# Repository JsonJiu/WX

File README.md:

# 云达诺项目 - V1.0.1

本仓库包含云达诺FM33LG0XX测试系统的代码。

## 目录结构

- **云达诺/** - 主项目代码目录
  - `Drivers/` - 驱动程序
  - `Inc/` - 头文件
  - `Src/` - 源代码文件
  - `MDK-ARM/` - Keil MDK工程文件
  - `MF-config/` - 配置文件
  - `README.md` - 项目说明
  - `README_V1.0.1.md` - V1.0.1版本更新说明

## 版本说明

当前版本：**V1.0.1**

查看详细更新内容：[云达诺/README_V1.0.1.md](./云达诺/README_V1.0.1.md)

## V1.0.1 主要更新

- ✅ 工位检测扩展至10个工位
- ✅ 新增独立阀门测试流程
- ✅ 优化阀门开关检测逻辑
- ✅ 压力检测功能更新
- ✅ 测试流程优化

## 快速开始

1. 克隆仓库
2. 使用Keil MDK打开 `云达诺/MDK-ARM/FM33LG0XX_Tester.uvprojx`
3. 编译并下载到目标设备

## 分支说明

- `main` - 主分支
- `v1.0.1` - V1.0.1版本分支

---

开发团队：云达诺开发组

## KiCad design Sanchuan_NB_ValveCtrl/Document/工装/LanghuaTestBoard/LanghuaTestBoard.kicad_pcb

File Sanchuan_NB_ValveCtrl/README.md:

# Sanchuan_NB_ValveCtrl

三川 NB-IoT 阀控水表测试工装程序

## 版本信息

- **当前版本**: 1.0.0
- **发布日期**: 2024-12-01
- **硬件平台**: FM33LG04x (Cortex-M0+)

## 项目说明

本项目为三川 NB-IoT 阀控水表的测试工装程序，用于生产线水表测试。

### 主要功能

- 水表通信协议测试
- 阀门控制测试
- 电流检测
- LED 状态指示
- 透传模式支持

## 编译环境

- **编译器**: ARM GCC 10 2021.10
- **构建系统**: CMake + Ninja
- **烧录工具**: PyOCD

## 快速开始

### Windows 编译

```bash
# 配置 (首次)
cmake.exe -S . -B build_fast -DCMAKE_BUILD_TYPE=Release -G Ninja

# 编译
cmake.exe --build build_fast --parallel

# 烧录
pyocd flash build_fast/Sanchuan_NB_ValveCtrl.elf --target fm33lg04x
```

### Linux 编译

```bash
# 配置 (首次)
cmake -S . -B build_fast -DCMAKE_BUILD_TYPE=Release -G Ninja

# 编译
cmake --build build_fast --parallel
```

## 目录结构

```
├── CMakeLists.txt      # CMake 构建配置
├── Src/                # 应用源代码
├── Inc/                # 应用头文件
├── Drivers/            # FM33LG0xx 驱动库
├── MF-config/          # 外设配置
├── VscodeGcc/          # VSCode + GCC 配置
├── MDK-ARM/            # Keil MDK 工程 (可选)
└── Document/           # 相关文档
```

## 版本历史

### v1.0.0 (2024-12-01)
- 初始版本
- 从浪花项目移植
- 重命名为 Sanchuan_NB_ValveCtrl

## 作者

Aspiring-Freeman

## 许可证

本项目基于 Mulan PSL v2 许可证开源。

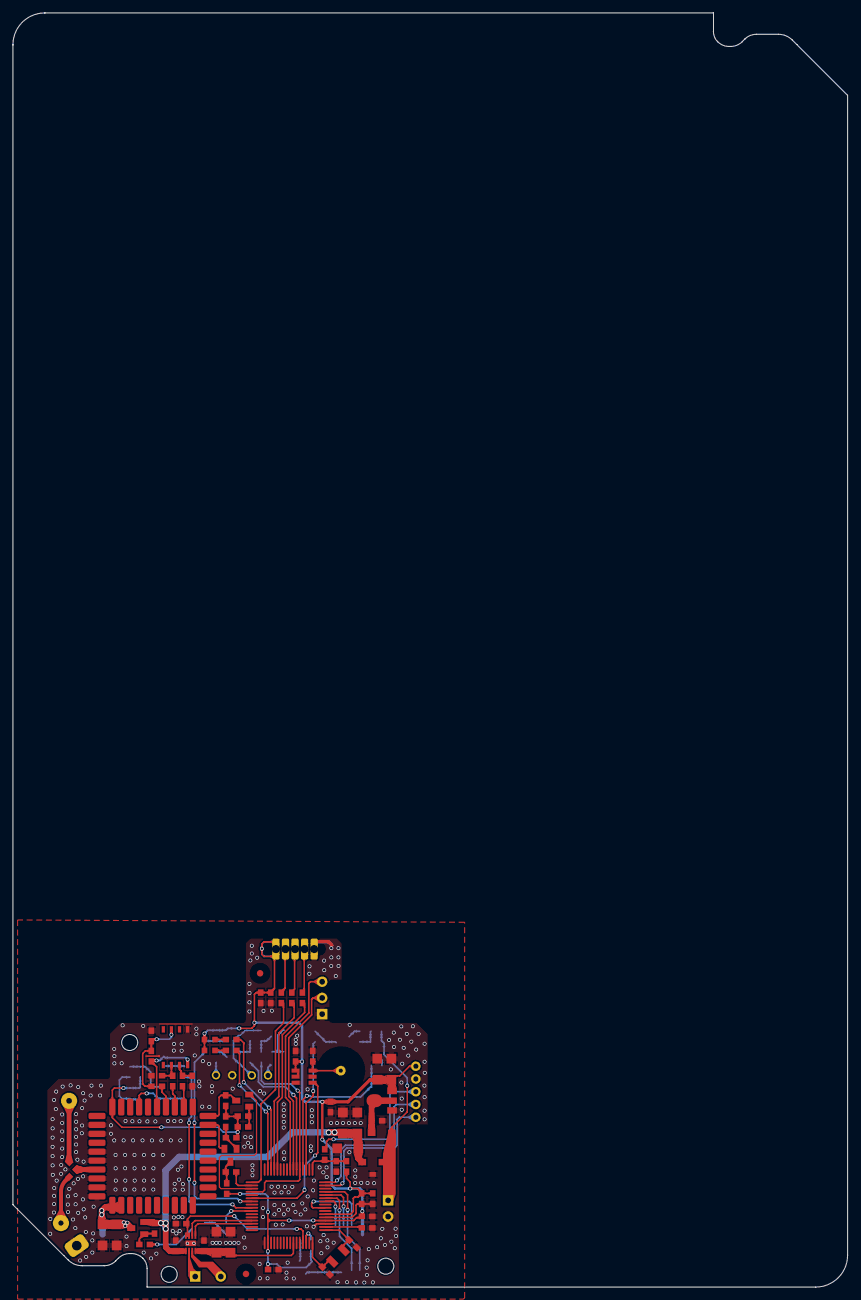
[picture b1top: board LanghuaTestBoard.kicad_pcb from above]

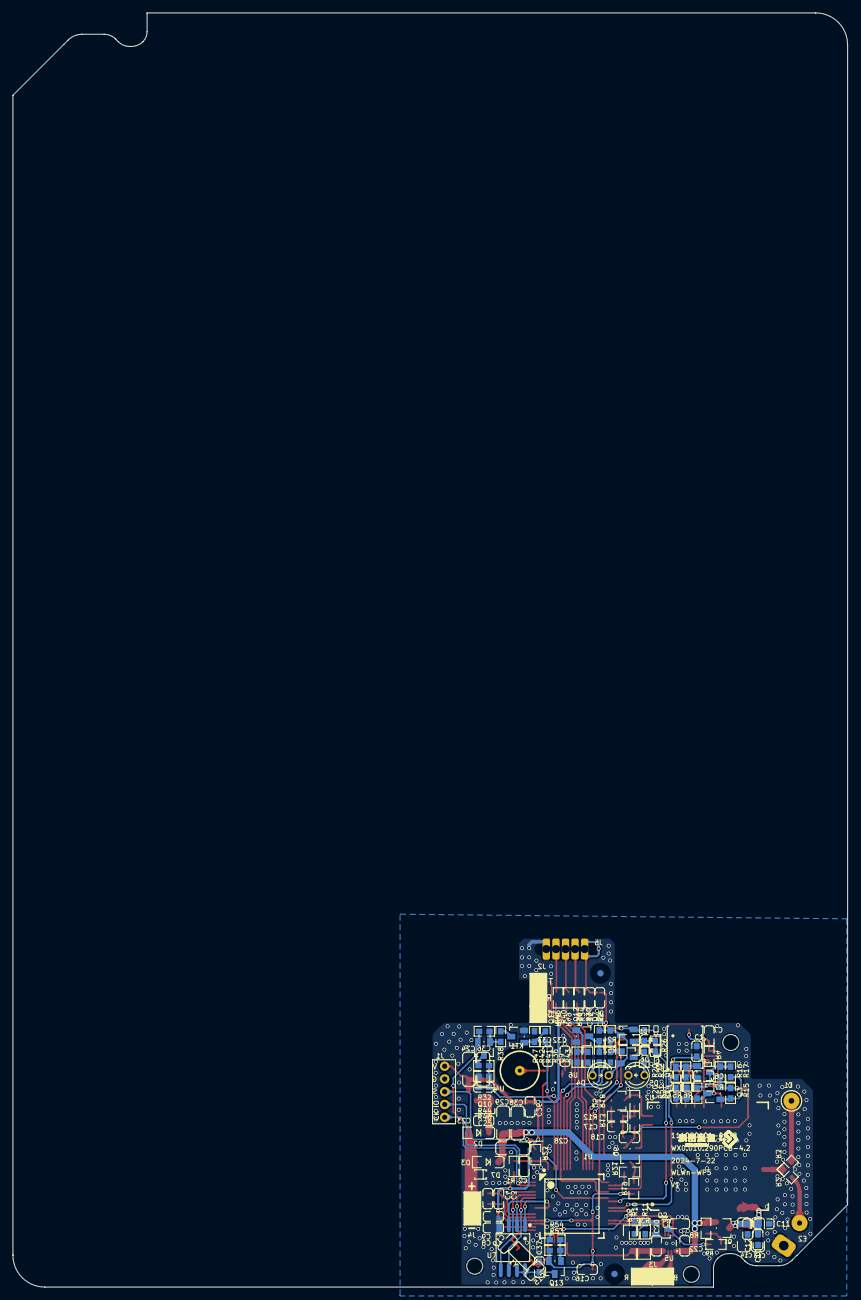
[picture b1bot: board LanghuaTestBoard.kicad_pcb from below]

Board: 2 copper layers, 130.8 x 199.7 mm, 126 parts (45 on the bottom side), 85 nets.

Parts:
C1, C2, C3, C8, C9, C12, C16, C21, C22, C26, C32, C34, C37: 100nF; C0603
C4: 10μF/10V; C0603
C5, C6, C7, C20: 33pF; C0603
C10, C15, C19: 22pF; C0603
C11, C23: 100pF; C0603
C13, C14, C24, C28, C29, C36, C38: 100uF; C1206
C17, C18: 1nF; C0603
C25: 12pF; C0603
C30: 10nF; C0603
C33: 4.7pF; C0603
C35: 1uF; C0603
D1, D6: Red; LED-0603
D2, D3: DSK14; SOD-123
D4: AT403; LED-3
D5: AT203-立; LED-3
D7: XE3D5VB; SOD-323_L1.8-W1.3-LS2.5-RD
E1: ANT-1
E2: ANTENNA_3; ANT-3
H1, H2, H4: HOLE-2.5
J1: CON5-2.0; J_DIP_2.0_1*05_H
J2: CON3; SIP-3
J3: CON2; SIP-2-4mm
J4: CON2; SIP-2
J5: BCON-B5
KT1: Touch; TOUCH-1
LABEL1, LABEL2, LABEL3, LABEL4: MARK
Q1, Q7, Q9, Q10: CJ2301; SOT-23
Q2, Q4, Q5, Q6, Q11, Q12: S8050; SOT-23
Q3, Q13: S8550; SOT-23
R1, R4, R9, R16, R18, R19, R38, R51, R54: 10kΩ±5%; R0603
R2, R3, R14, R21, R23, R41: 0Ω±5%; R0603
R5, R6, R7: 22Ω±5%; R0603
R8, R53: 200KΩ±5%; R0603
R10, R12, R13, R17, R20, R40: 4.7kΩ±5%; R0603
R11, R15, R22, R45, R47: 47K±5%; R0603
R24, R26, R36, R52: 1kΩ±5%; R0603
R25, R30, R32: 1MΩ±5%; R0603
R34: 100kΩ±5%; R0603
R35, R37: 1Ω±1%; R1206
R42: 20kΩ±5%; R0603
R43, R48, R49, R50: 100Ω±5%; R0603
R44: 20K±1%; R0603
R46: 10kΩ±1%; R0603
U1: FM33LE026; LQFP-64_L10.0-W10.0-P0.50-LS12.0-BL
U2: UMN601-M1; MB26-Y0B
U3: ESIM; MFF2
U4: CE6232A33P; SOT89
U5: DRV8837; WSON-8
U6: TTP233H; SOT-23-6
U7: P25Q32H-SUH-IR; SOIC-8
Y1: 32.768K; Y3215

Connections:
AIN8: C30.2, R35.2, R37.2, U1.42, U5.4
ANT: R2.1, R3.2, U2.27
CTR_F_VCC: R54.1, U1.46
DB_RXD: J2.2, U1.7
DB_TXD: J2.3, U1.8
DRV+: J3.1, U5.2
DRV-: J3.2, U5.3
EXTI1: R48.1, U1.12
EXTI2: R49.1, U1.13
EXTI3: R50.1, U1.17
EXTI4: R41.2, U1.5, U1.20
FLASH_CLK: U1.59, U7.6
FLASH_CS: U1.58, U7.1
FLASH_MISO: U1.60, U7.2
FLASH_MOSI: U1.61, U7.5
FLASH_VCC: C37.2, Q13.3, U7.7, U7.8
FLASH_WP: U1.56, U7.3
GND: C1.1, C2.1, C3.1, C4.1, C5.1, C6.1, C7.2, C8.1, C9.1, C10.1, C11.1, C12.1, C13.1, C14.1, C15.1, C16.1, C19.1, C20.1, C21.1, C22.2, C23.1, C24.1, C25.1, C26.1, C28.1, C29.1, C30.1, C32.2, C33.1, C34.1, C35.1, C36.1, C37.1, C38.1, D5.2, D7.1, E2.2, J1.2, J2.1, J4.2, J5.1, Q2.2, Q4.2, Q11.2, Q12.2, R11.1, R22.1, R35.1, R37.1, R45.1, R46.2, R47.1, R51.1, U1.33, U1.51, U1.53, U2.22, U2.23, U2.25, U2.26, U2.28, U2.29, U2.30, U3.1, U4.1, U5.0, U6.2, U6.6, U7.4
IR_EN: R26.1, U1.23
IR_TX: R36.1, U1.6
KEY: U1.22, U6.1
LED0: R24.2, U1.14
LED1: R52.2, U1.15
NB_ON: R10.1, U1.26
NB_RST: C20.2, Q3.3, R14.2, R51.2, U2.17
NB_RST_MCU: R20.2, U1.25
NB_RX: Q5.3, R18.1, U2.10
NB_RX_MCU: R21.2, U1.18
NB_TX: Q6.2, U2.9
NB_TX_MCU: Q5.2, U1.19
NetC5_2: C5.2, R5.1, U3.7
NetC6_2: C6.2, R6.1, U3.6
NetC7_1: C7.1, R4.1, R7.1, U3.3
NetC8_2: C8.2, U1.50
NetC17_1: C17.1, Q5.1, R12.2
NetC18_2: C18.2, Q6.1, R13.1
NetC23_2: C23.2, D2.2, U4.3
NetC33_2: C33.2, KT1.1, U6.3
NetD1_2: D1.2, R24.1
NetD4_1: D4.1, R42.2
NetD4_2: D4.2, Q7.3, Q9.2, R30.2, R34.2
NetD5_1: D5.1, R43.1
NetD6_2: D6.2, R52.1
NetE1_1: E1.1, R3.1
NetE2_1: E2.1, R2.2
NetJ1_3: J1.3, R23.2
NetJ5_2: J5.2, R48.2
NetJ5_3: J5.3, R49.2
NetJ5_4: J5.4, R50.2
NetQ1_1: Q1.1, R8.1, R9.2
NetQ2_1: Q2.1, R10.2, R11.2
NetQ2_3: Q2.3, R9.1
NetQ3_1: Q3.1, R15.1, R17.2
NetQ4_1: Q4.1, R20.1, R22.2
NetQ4_3: Q4.3, R14.1, R16.1, R17.1
NetQ6_3: Q6.3, R19.2, R21.1
NetQ7_1: Q7.1, R25.1, R26.2
NetQ9_1: Q9.1, R30.1, R36.2
NetQ9_3: Q9.3, R43.2
NetQ10_1: Q10.1, R32.1, R38.2
NetQ10_3: Q10.3, R44.1
NetQ11_1: Q11.1, R40.2, R45.2
NetQ11_3: Q11.3, R38.1
NetQ12_1: Q12.1, R42.1, R47.2
NetQ12_3: Q12.3, R34.1, R41.1
NetQ13_1: Q13.1, R53.1, R54.2
NetR5_2: R5.2, U2.12
NetR6_2: R6.2, U2.13
NetR7_2: R7.2, U2.14
OUT_A: U1.29, U5.6
OUT_B: U1.30, U5.5
OUT_EN: C21.2, U1.45, U5.7, U5.8
RESET: C2.2, R1.1, R23.1, U1.1
SVS: C25.2, R44.2, R46.1, U1.4
SVS_EN: R40.1, U1.3
SWCLK: J1.5, U1.63
SWDIO: J1.4, U1.64
USIM_VDD: C1.2, R4.2, U2.15, U3.8
VBAT: D2.1, D3.1, D7.2, J4.1, Q10.2, R32.2
VCC: C3.2, C4.2, C9.2, C16.2, C24.2, C26.2, C32.1, C34.2, C35.2, C36.2, D1.1, D6.1, J1.1, J5.5, Q7.2, Q13.2, R1.2, R19.1, R25.2, R53.2, U1.34, U1.52, U1.54, U4.2, U6.4, U6.5
VCC_M: C22.1, C28.2, C29.2, C38.2, D3.2, Q1.2, R8.2, U5.1
VDD_IO: C17.2, C18.1, Q3.2, R12.1, R13.2, R15.2, R16.2, R18.2, U2.20
VDD_NB: C10.2, C11.2, C12.2, C13.2, C14.2, Q1.3, U2.31, U2.32
XT1: C15.2, U1.48, Y1.2
XT2: C19.2, U1.49, Y1.1

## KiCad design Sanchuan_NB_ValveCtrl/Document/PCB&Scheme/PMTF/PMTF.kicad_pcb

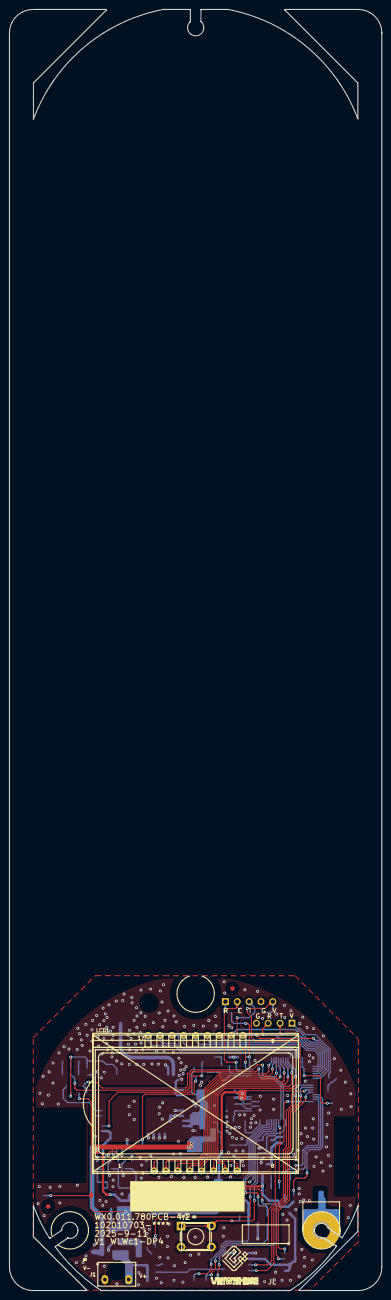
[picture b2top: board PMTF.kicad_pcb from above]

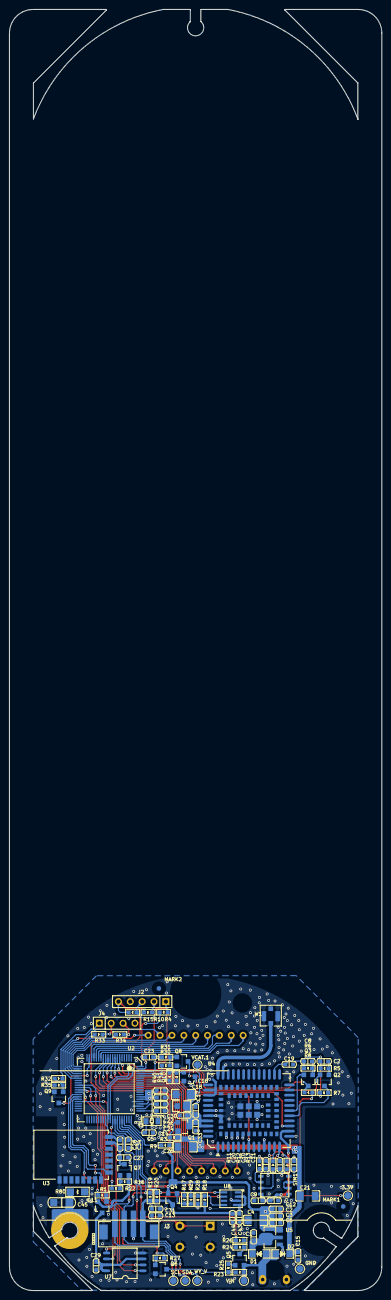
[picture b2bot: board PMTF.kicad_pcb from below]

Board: 2 copper layers, 79.7 x 274.3 mm, 109 parts (106 on the bottom side), 86 nets.

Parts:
3.3V: TEST-PAD
*1: Bar Code1
C1, C2, C9, C13, C15, C22, C24, C25, C29, C30: 100nF/50V; CAP0603
C3, C27, C31, C43: 10uF/10V; CAP0603
C4, C16, C21, C26: 100uF/6.3V; GRM1206
C5, C14: 12pF/50V; CAP0603
C6: 22pF/50V; CAP0603
C7, C8: 1nF/50V; CAP0603
C10, C11, C12, C17, C20, C23, C44: 33pF/50V; CAP0603
C18: 22uF/10V; CAP0805
C19, C28: 1uF/16V; CAP0603
C33, C34: 10pF/50V; CAP0603
C45: 103P/1KV; CAP1206
D1, D2: DS36W; SOD-123FL
GND: TEST-PAD
J1: Header 2; VBAT
J2: Header 5; PIN254_1*5SR
J3: CON4; WX-PH-4AB
J4: XH254_4P; HDR1X4_2.54
LCD1: LCD; JR-H25903AFP
MARK1, MARK2: MARK
Q1, Q4, Q7: UT3401ZG; SOT-23
Q2, Q3, Q6, Q8, Q9, Q10: NPNS-9013; SOT-23
Q5, Q11: PNPS-9012; SOT-23
R1, R30, R32, R40: 3K 5%; RES0603
R3, R16, R17: 2M 5%; RES0603
R4: 100R 5%; RES0603
R5, R6, R7, R8: 4.7K 5%; RES0603
R9, R22, R29: 200K 5%; RES0603
R10, R15, R18, R28: 10K 1%; RES0603
R11, R12, R13: 22R 5%; RES0603
R19, R20, R31, R41: 10K 5%; RES0603
R23: 200k; RES0603
R24: 330K 5%; RES0603
R25, R27: 10k; RES0603
R26: 220K 5%; RES0603
R33, R34, R35: 1K 5%; RES0603
R80: 1M 5%; RES1206
SCL: TEST-PAD
SDA: TEST-PAD
SIM1: SIM IC; SIMIC
SW1: KEY; DIP-6X6X8
U2: FM33LG0x8; LQFP80
U3: DB809
U4: EC801E
U5: CE6232A33P; SOT-89
U7: P25Q80H-SUH-IR; SOP-8L-200MIL
U8: HP303B; LGA_8
VCAT.1: TEST-PAD
VIN: TEST-PAD
W1: 天线; ANT-IPEX_1
WY_V: TEST-PAD
Y1: SF32WK32768D71T005; SMD-3215_2P

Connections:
3.3V: 3.3V.1, C2.1, C3.1, C4.1, C6.1, C22.2, C25.2, J2.5, Q4.2, Q7.2, Q11.2, R8.2, R10.2, R15.1, R16.2, R17.2, U2.64, U2.66, U2.67, U5.3
CAT.1-RESET: Q8.3, U4.15
CAT.1-RXD: Q2.3, R7.1, U4.17
CAT.1-TXD: Q3.2, U4.18
CAT.1_KEY: R40.1, U2.76
CAT.1_PWR: R9.1, U2.57
CAT.1_VCC: C16.1, C17.1, C18.1, C30.2, C33.1, Q1.3, U4.42, U4.43, VCAT.1.1
CAT.1_VIN: C15.1, C21.1, C26.1, D2.2, Q1.2, R3.2
CHEAK_POWER: R27.1, U2.52
COM0: LCD1.1, U2.6
COM1: LCD1.2, U2.7
COM2: LCD1.3, U2.8
COM3: LCD1.4, U2.9
EARTH: C45.1, R80.2
FLASH_CLK: U2.30, U7.6
FLASH_CS: U2.29, U7.1
FLASH_CTL: R1.1, U2.33
FLASH_MISO: U2.31, U7.2
FLASH_MOSI: U2.32, U7.5
GND: C1.2, C2.2, C3.2, C4.2, C5.1, C6.2, C9.2, C10.1, C11.1, C12.2, C13.2, C14.1, C15.2, C16.2, C17.2, C18.2, C19.2, C20.1, C21.2, C22.1, C23.1, C24.2, C25.1, C26.2, C27.2, C28.2, C29.2, C30.1, C31.2, C33.2, C34.1, C43.2, C44.2, C45.2, GND.1, J1.1, J2.4, J3.2, J3.5, J3.6, J4.4, Q6.2, Q8.2, Q9.2, Q10.2, R26.1, R28.2, R31.1, R35.1, R41.2, R80.1, SIM1.1, SW1.2, U2.63, U2.65, U3.1, U3.15, U4.1, U4.10, U4.27, U4.34, U4.36, U4.37, U4.40, U4.41, U4.45, U4.46, U4.47, U4.48, U4.70, U4.71, U4.72, U4.73, U4.88, U4.89, U4.90, U4.91, U4.92, U4.93, U4.94, U4.95, U5.1, U7.4, U8.2, W1.2
GPRS_RST: R30.1, U2.77
LVDIN: C34.2, R24.1, R26.2, U2.53
MCU_RXD2: Q3.3, R8.1, U2.50
MCU_TXD2: Q2.2, U2.51
NetC1_1: C1.1, D1.2, U5.2
NetC7_2: C7.2, Q2.1, R5.2
NetC8_2: C8.2, Q3.1, R6.2
NetC24_1: C24.1, U2.62
NetC27_1: C27.1, C28.1, Q7.3, U3.14
NetC29_1: C29.1, Q11.3, U7.3, U7.7, U7.8
NetJ2_1: J2.1, R4.2
NetJ4_1: J4.1, R32.1
NetJ4_2: J4.2, R33.1
NetJ4_3: J4.3, R34.1
NetQ1_1: Q1.1, R3.1, R9.2
NetQ4_1: Q4.1, R17.1, R29.2
NetQ5_1: Q5.1, R25.2
NetQ5_3: Q5.3, R24.2
NetQ6_1: Q6.1, R27.2
NetQ6_3: Q6.3, R23.1, R25.1
NetQ7_1: Q7.1, R16.1, R22.2
NetQ8_1: Q8.1, R30.2, R31.2
NetQ9_1: Q9.1, R32.2, R35.2
NetQ10_1: Q10.1, R40.2, R41.1
NetQ11_1: Q11.1, R1.2
NetR18_1: R18.1, R28.1, U8.8
NetU4_35: U4.35, W1.1
PWRKEY: Q10.3, U4.7
RST: C23.2, R4.1, U2.80
RXD1: U2.34, U3.9
RXD4: R34.2, U2.23
SEG0: LCD1.5, U2.10
SEG1: LCD1.6, U2.11
SEG2: LCD1.7, U2.12
SEG3: LCD1.8, U2.13
SEG4: LCD1.9, U2.26
SEG5: LCD1.10, U2.25
SEG6: LCD1.11, U2.22
SEG7: LCD1.12, U2.21
SEG8: LCD1.13, U2.18
SEG9: LCD1.14, U2.17
SEG10: LCD1.15, U2.16
SEG11: LCD1.16, U2.15
SEG12: LCD1.17, U2.14
SET: Q9.3, U2.19
SIM_CLK: C20.2, R11.2, SIM1.6
SIM_DATA: C11.2, R13.2, SIM1.2, SIM1.3
SIM_RST: C10.2, R12.2, SIM1.7
SIM_VDD: C9.1, C12.1, SIM1.8, U4.14
SWCLK: J2.2, R10.1, U2.78
SWIO: J2.3, R15.2, U2.79
SWITCH: C13.1, SW1.1, U2.49
TXD1: U2.35, U3.8
TXD4: R33.2, U2.24
USIM_CLK: R11.1, U4.13
USIM_DATA: R13.1, U4.11
USIM_RST: R12.1, U4.12
VDD_BLE_CTL: R22.1, U2.36
VDD_EXT: C7.1, C8.1, C19.1, R5.1, R6.1, R7.2, U4.24
VIN: D1.1, D2.1, J1.2, Q5.2, R23.2, VIN.1
WY_CTR: R29.1, U2.54
WY_SCL: J3.4, R20.1, SCL.1, U2.56, U8.5
WY_SDA: J3.3, R19.1, SDA.1, U2.55, U8.6
WY_VCC: C31.1, C43.1, C44.1, J3.1, Q4.3, R18.2, R19.2, R20.2, U8.1, U8.3, WY_V.1
XT1: C14.2, U2.61, Y1.1
XT2: C5.2, U2.60, Y1.2

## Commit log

2025-11-27 Initial commit: Add project files
2025-11-27 Add 云达诺 project
2025-11-27 Initial commit: Add Program project files
2025-11-27 Rename Program folder to 华润星闪
2025-12-05 Release V1.0.1: 工位扩展、阀门测试优化、压力检测功能更新
2025-12-05 添加根目录README,便于GitHub显示
2025-12-08 更新云达诺项目到v1.0.2版本
2025-12-10 电磁阀控制器
2025-12-10 深燃增加开盖倾斜
2025-12-10 大口径水表
2025-12-10 民膜星闪
2025-12-10 华润安全模组
2025-12-10 水平立式无磁
2025-12-18 增加无磁信号强度测试
2025-12-18 星闪119
2025-12-18 老通用商超
2025-12-29 123123
2025-12-30 安徽美硕带工位透传
2026-01-05 带AT指令发送和解析
2026-01-08 PC串口实时打印调试信息
2026-01-08 AT指令
2026-01-08 添加三川NB阀控项目
2026-01-08 任务书 硬件带硬件流程图
2026-01-12 删除云达诺文件夹
2026-01-12 云达诺最终
2026-01-12 新商超气表程序——深燃定制
2026-01-12 民用超声——孟工
2026-01-12 商超程序——孟工
2026-03-25 chore: add 荣鑫民膜 folder
2026-03-30 11楼民超工装程序
2026-03-30 自动化工装程序
